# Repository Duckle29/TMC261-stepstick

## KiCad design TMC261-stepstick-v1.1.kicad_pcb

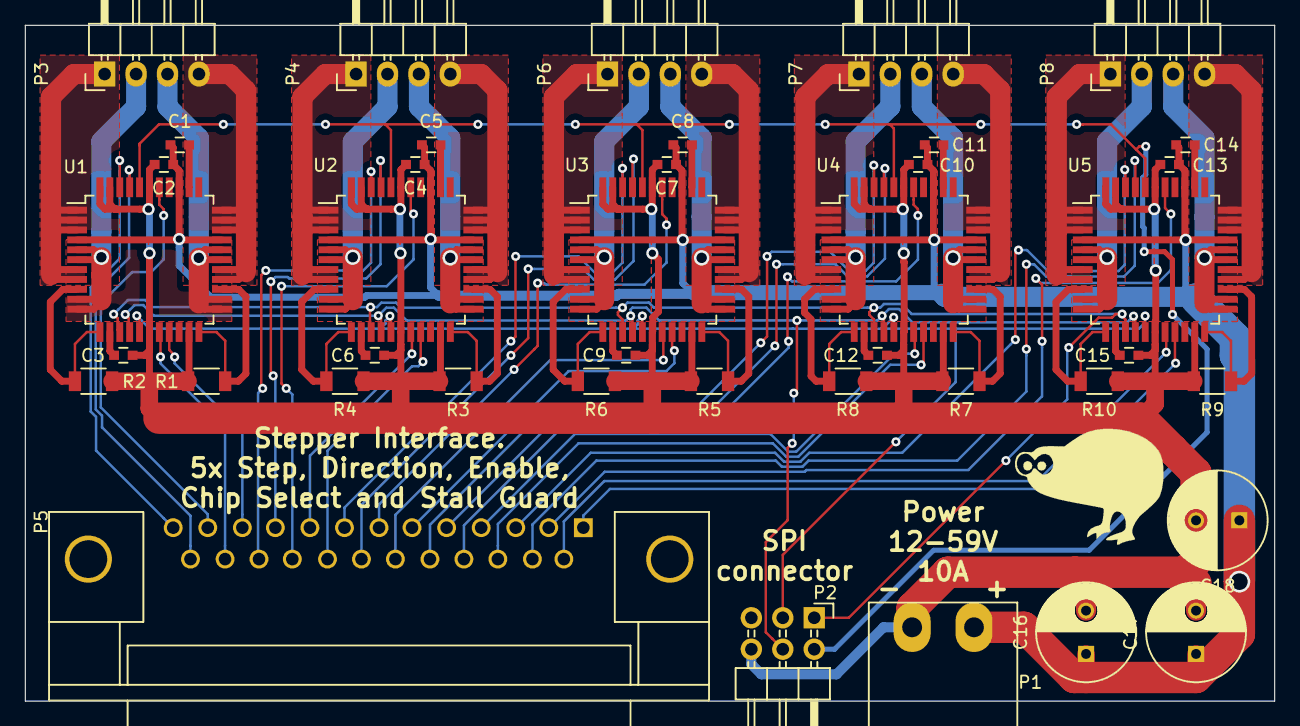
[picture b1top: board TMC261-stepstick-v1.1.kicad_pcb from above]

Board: 2 copper layers, 101.0 x 54.6 mm, 41 parts (0 on the bottom side), 71 nets.

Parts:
C1, C2, C4, C5, C7, C8, C10, C11, C13, C14: 100nF; C_0603
C3, C6, C9, C12, C15: 470nF; C_0603
C16, C17, C18: CP_Small; C_Radial_D8_L11.5_P3.5
P1: CONN_01X02; 20020110-G021ALF
P2: CONN_02X03; Pin_Header_Angled_2x03
P3, P4, P6, P7, P8: CONN_01X04; Pin_Header_Angled_1x04
P5: CONN_01X25; DB25FC
R1, R2, R3, R4, R5, R6, R7, R8, R9, R10: 150mR; C_1206
U1, U2, U3, U4, U5: TMC261; LQFP-44_10x10mm_Pitch0.8mm

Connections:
GND: C2.2, C3.2, C4.2, C6.2, C7.2, C9.2, C10.2, C12.2, C13.2, C15.2, C16.2, C17.2, C18.2, P1.1, P2.6, R1.2, R2.2, R3.2, R4.2, R5.2, R6.2, R7.2, R8.2, R9.2, R10.2, U1.17, U1.21, U1.39, U1.43, U1.44, U2.17, U2.21, U2.39, U2.43, U2.44, U3.17, U3.21, U3.39, U3.43, U3.44, U4.17, U4.21, U4.39, U4.43, U4.44, U5.17, U5.21, U5.39, U5.43, U5.44
M1_A1: P3.1, U1.1, U1.2, U1.3, U1.7, U1.8
M1_A2: P3.2, U1.5, U1.6, U1.10, U1.11
M1_B1: P3.4, U1.26, U1.27, U1.31, U1.32, U1.33
M1_B2: P3.3, U1.23, U1.24, U1.28, U1.29
M1_CSN: P5.24, U1.18
M1_DIR: P5.25, U1.41
M1_SG: P5.12, U1.38
M1_STEP: P5.13, U1.42
M2_A1: P4.1, U2.1, U2.2, U2.3, U2.7, U2.8
M2_A2: P4.2, U2.5, U2.6, U2.10, U2.11
M2_B1: P4.4, U2.26, U2.27, U2.31, U2.32, U2.33
M2_B2: P4.3, U2.23, U2.24, U2.28, U2.29
M2_CSN: P5.9, U2.18
M2_DIR: P5.10, U2.41
M2_SG: P5.22, U2.38
M2_STEP: P5.23, U2.42
M3_A1: P6.1, U3.1, U3.2, U3.3, U3.7, U3.8
M3_A2: P6.2, U3.5, U3.6, U3.10, U3.11
M3_B1: P6.4, U3.26, U3.27, U3.31, U3.32, U3.33
M3_B2: P6.3, U3.23, U3.24, U3.28, U3.29
M3_CSN: P5.19, U3.18
M3_DIR: P5.20, U3.41
M3_SG: P5.7, U3.38
M3_STEP: P5.8, U3.42
M4_A1: P7.1, U4.1, U4.2, U4.3, U4.7, U4.8
M4_A2: P7.2, U4.5, U4.6, U4.10, U4.11
M4_B1: P7.4, U4.26, U4.27, U4.31, U4.32, U4.33
M4_B2: P7.3, U4.23, U4.24, U4.28, U4.29
M4_CSN: P5.4, U4.18
M4_DIR: P5.5, U4.41
M4_SG: P5.17, U4.38
M4_STEP: P5.18, U4.42
M5_A1: P8.1, U5.1, U5.2, U5.3, U5.7, U5.8
M5_A2: P8.2, U5.5, U5.6, U5.10, U5.11
M5_B1: P8.4, U5.26, U5.27, U5.31, U5.32, U5.33
M5_B2: P8.3, U5.23, U5.24, U5.28, U5.29
M5_CSN: P5.14, U5.18
M5_DIR: P5.15, U5.41
M5_SG: P5.2, U5.38
M5_STEP: P5.3, U5.42
MISO: P2.1, U1.14, U2.14, U3.14, U4.14, U5.14
MOSI: P2.4, U1.15, U2.15, U3.15, U4.15, U5.15
unnamed: C1.2, U1.35
unnamed: C3.1, U1.13
unnamed: C5.2, U2.35
unnamed: C6.1, U2.13
unnamed: C8.2, U3.35
unnamed: C9.1, U3.13
unnamed: C11.2, U4.35
unnamed: C12.1, U4.13
unnamed: C14.2, U5.35
unnamed: C15.1, U5.13
unnamed: R1.1, U1.22, U1.25
unnamed: R2.1, U1.9, U1.12
unnamed: R3.1, U2.22, U2.25
unnamed: R4.1, U2.9, U2.12
unnamed: R5.1, U3.22, U3.25
unnamed: R6.1, U3.9, U3.12
unnamed: R7.1, U4.22, U4.25
unnamed: R8.1, U4.9, U4.12
unnamed: R9.1, U5.22, U5.25
unnamed: R10.1, U5.9, U5.12
SCK: P2.3, U1.16, U2.16, U3.16, U4.16, U5.16
VDD: P2.2, U1.40, U2.40, U3.40, U4.40, U5.40
VPP: C1.1, C2.1, C4.1, C5.1, C7.1, C8.1, C10.1, C11.1, C13.1, C14.1, C16.1, C17.1, C18.1, P1.2, U1.4, U1.30, U1.36, U2.4, U2.30, U2.36, U3.4, U3.30, U3.36, U4.4, U4.30, U4.36, U5.4, U5.30, U5.36
~M1_EN: P5.11, U1.19
~M2_EN: P5.21, U2.19
~M3_EN: P5.6, U3.19
~M4_EN: P5.16, U4.19
~M5_EN: P5.1, U5.19

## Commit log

2016-09-15 Intial commit
